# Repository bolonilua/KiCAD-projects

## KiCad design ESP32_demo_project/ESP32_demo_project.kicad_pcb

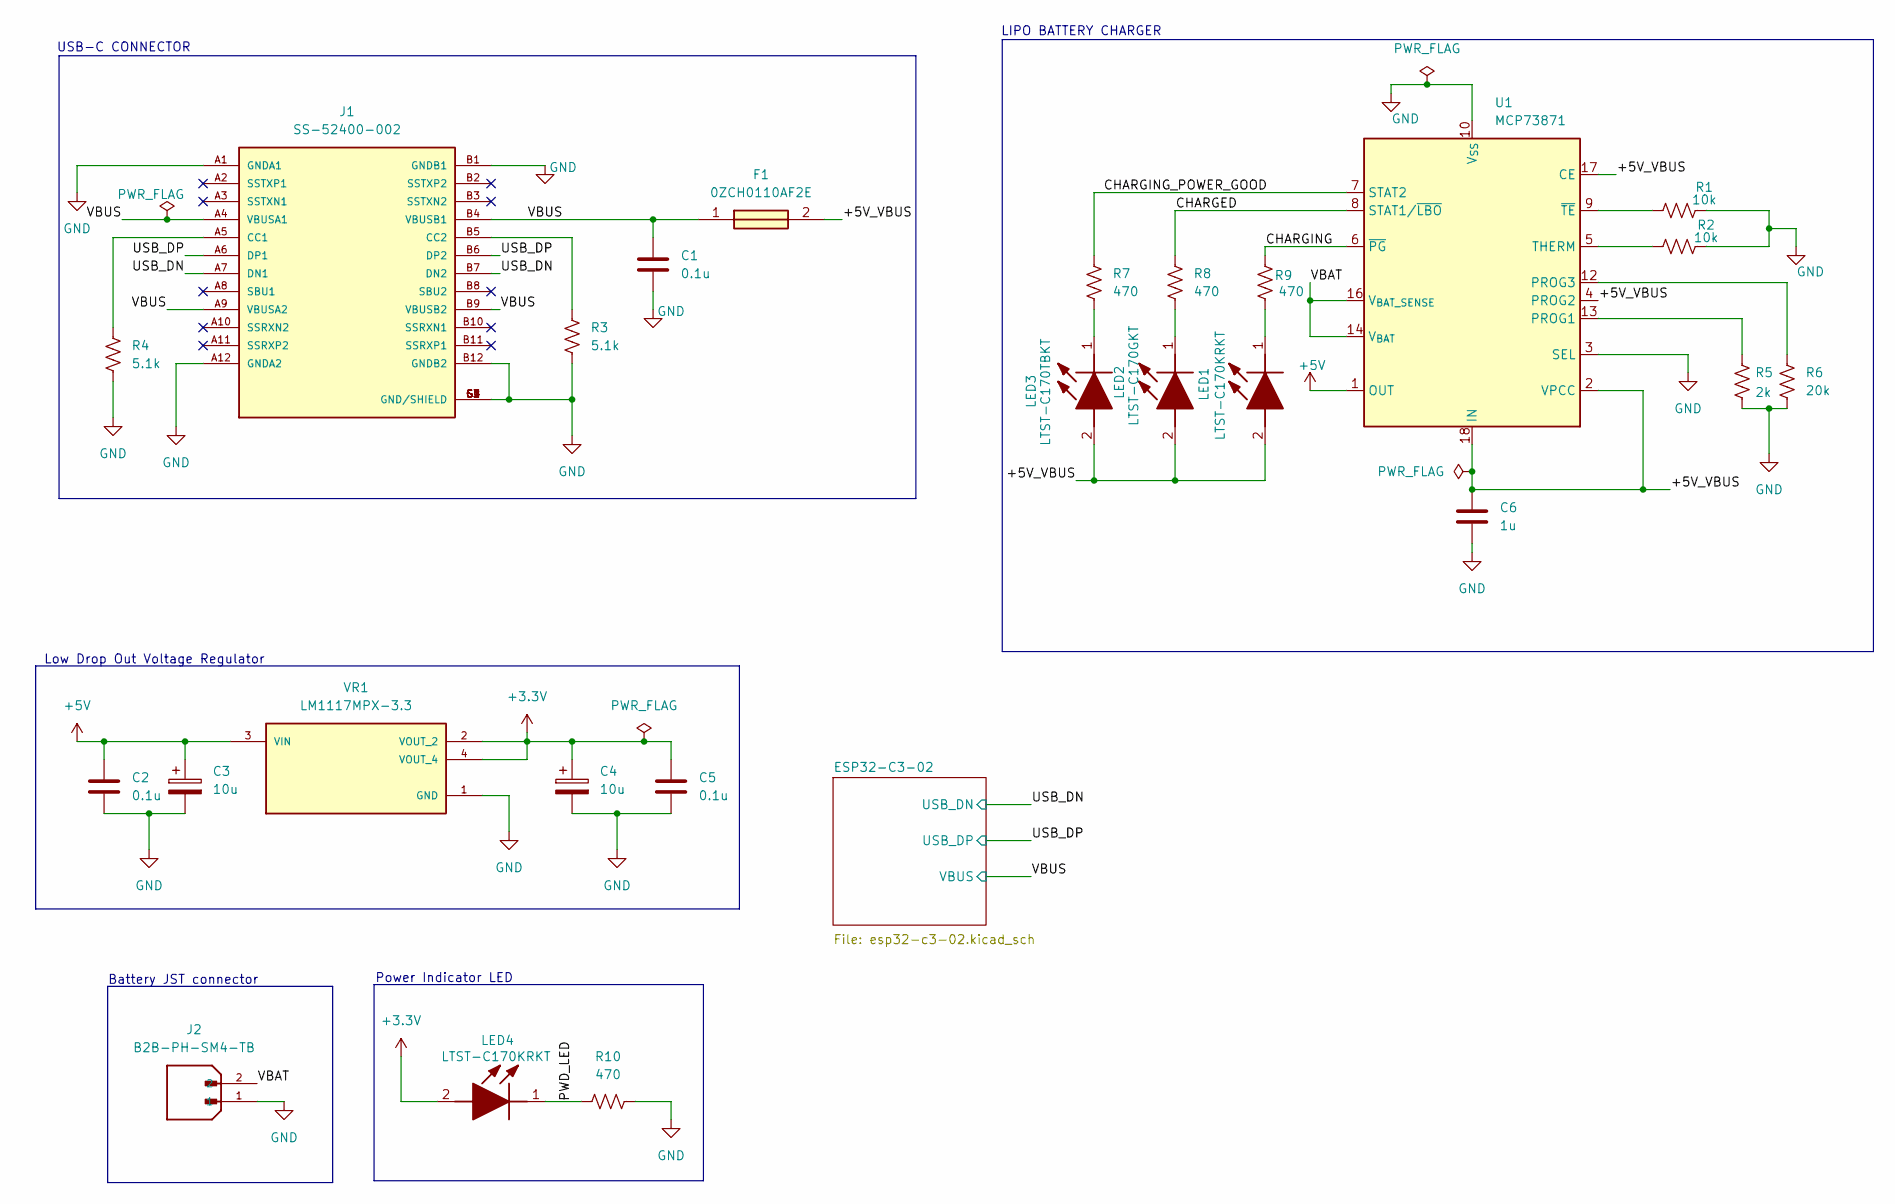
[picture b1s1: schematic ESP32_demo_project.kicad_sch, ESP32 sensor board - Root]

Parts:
C1, C2, C5: 0.1u; C_0805_2012Metric
C3, C4: 10u; T491A
C6: 1u; C_0805_2012Metric
F1: 0ZCH0110AF2E; FUSC3226X100N; Manufacturer_Part_Number 0ZCH0110AF2E
J1: SS-52400-002; BELFUSE_SS-52400-002; PARTREV A0
J2: B2B-PH-SM4-TB; JST_B2B-PH-SM4-TB; PARTREV N/A
LED1, LED4: LTST-C170KRKT; LEDC2012X120N; Manufacturer_Part_Number LTST-C170KRKT; Mouser Part Number 859-LTST-C170KRKT
LED2: LTST-C170GKT; LEDC2012X120N; Manufacturer_Part_Number LTST-C170GKT; Mouser Part Number 859-LTST-C170GKT
LED3: LTST-C170TBKT; LEDC2012X120N; Manufacturer_Part_Number LTST-C170TBKT; Mouser Part Number 859-LTST-C170TBKT
R1, R2: 10k; R_0805_2012Metric
R3, R4: 5.1k; R_0805_2012Metric
R5: 2k; R_0805_2012Metric
R6: 20k; R_0805_2012Metric
R7, R8, R9, R10: 470; R_0805_2012Metric
U1: MCP73871; QFN-20-1EP_4x4mm_P0.5mm_EP2.5x2.5mm
VR1: LM1117MPX-3.3; VREG_LM1117MPX-3.3

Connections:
+3.3V: C4.1, C5.1, LED4.2 (A), VR1.2 (VOUT_2), VR1.4 (VOUT_4); also elsewhere on the board
+5V: C2.1, C3.1, U1.1 (OUT), U1.20 (OUT), VR1.3 (VIN)
/+5V_VBUS: C6.1, F1.2, LED1.2 (A), LED2.2 (A), LED3.2 (A), U1.2 (VPCC), U1.4 (PROG2), U1.17 (CE), U1.18 (IN), U1.19 (IN)
/CHARGED: R8.1, U1.8 (STAT1/~LBO)
/CHARGING: R9.1, U1.6 (~PG)
/CHARGING_POWER_GOOD: R7.1, U1.7 (STAT2)
/PWD_LED: LED4.1 (K), R10.1
/USB_DN: J1.A7 (DN1), J1.B7 (DN2); also elsewhere on the board
/USB_DP: J1.A6 (DP1), J1.B6 (DP2); also elsewhere on the board
/VBAT: J2.2, U1.14 (V_{BAT}), U1.15 (V_{BAT}), U1.16 (V_{BAT_SENSE})
/VBUS: C1.1, F1.1, J1.A4 (VBUSA1), J1.A9 (VBUSA2), J1.B4 (VBUSB1), J1.B9 (VBUSB2); also elsewhere on the board
GND: C1.2, C2.2, C3.2, C4.2, C5.2, C6.2, J1.A1 (GNDA1), J1.A12 (GNDA2), J1.B1 (GNDB1), J1.B12 (GNDB2), J1.G1 (GND/SHIELD), J1.G2 (GND/SHIELD), J1.G3 (GND/SHIELD), J1.G4 (GND/SHIELD), J1.S1 (GND/SHIELD), J1.S2 (GND/SHIELD), J1.S3 (GND/SHIELD), J1.S4 (GND/SHIELD), J2.1, R1.2, R2.2, R3.2, R4.2, R5.2, R6.1, R10.2, U1.3 (SEL), U1.10 (V_{SS}), U1.11 (V_{SS}), U1.21 (V_{SS}), VR1.1 (GND); also elsewhere on the board
unnamed: J1.A5 (CC1), R4.1
unnamed: J1.B5 (CC2), R3.1
unnamed: LED1.1 (K), R9.2
unnamed: LED2.1 (K), R8.2
unnamed: LED3.1 (K), R7.2
unnamed: R5.1, U1.13 (PROG1)
unnamed: R6.2, U1.12 (PROG3)
unnamed: R2.1, U1.5 (THERM)
unnamed: R1.1, U1.9 (~TE)

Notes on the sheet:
LIPO BATTERY CHARGER
Power Indicator LED
Battery JST connector
Low Drop Out Voltage Regulator
USB-C CONNECTOR

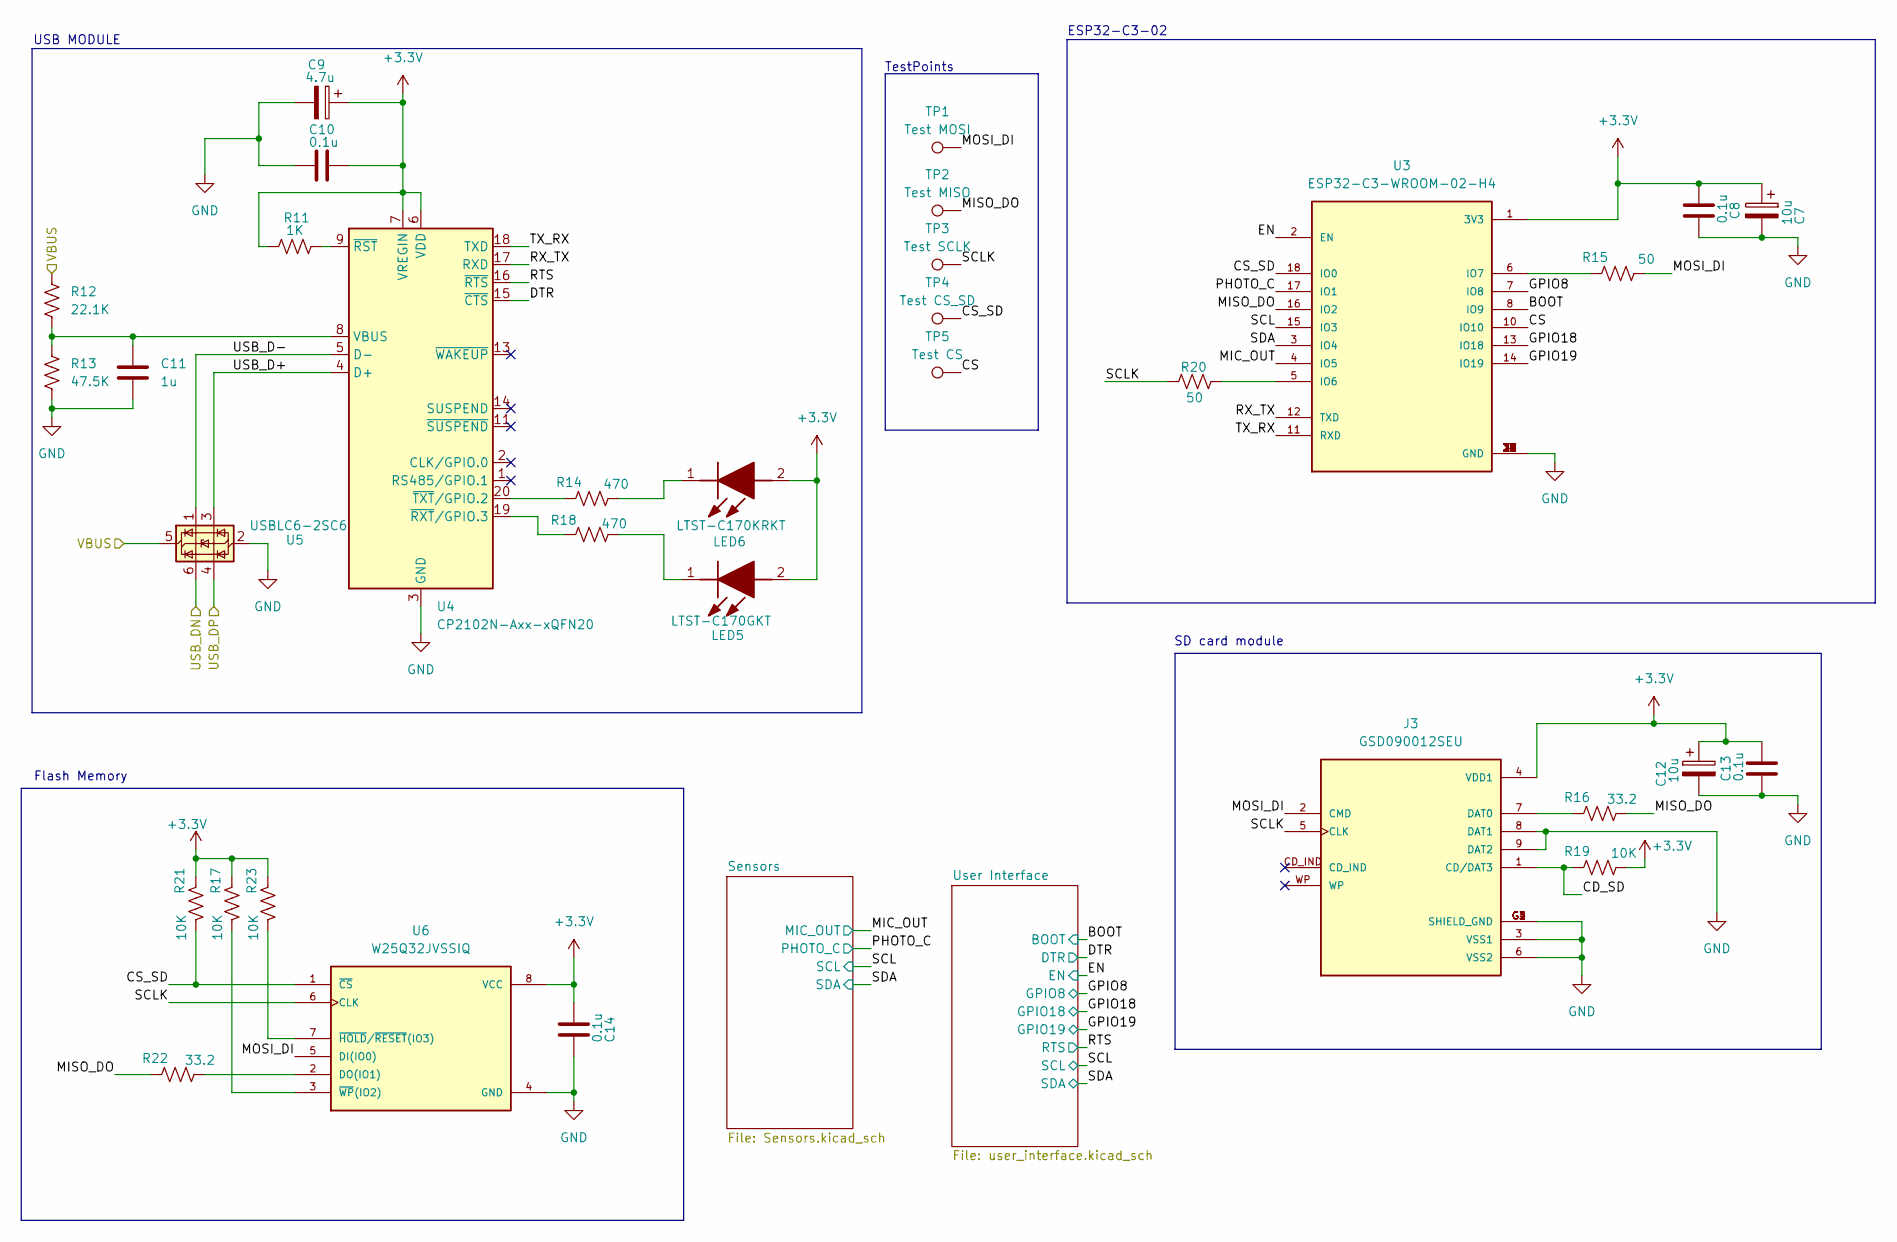
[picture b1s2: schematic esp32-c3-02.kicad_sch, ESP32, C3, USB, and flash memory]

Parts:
C7, C12: 10u; T491A
C8, C10, C13, C14: 0.1u; C_0805_2012Metric
C9: 4.7u; T491A
C11: 1u; C_0805_2012Metric
J3: GSD090012SEU; AMPHENOL_GSD090012SEU; PARTREV E
LED5: LTST-C170GKT; LEDC2012X120N; Manufacturer_Part_Number LTST-C170GKT; Mouser Part Number 859-LTST-C170GKT
LED6: LTST-C170KRKT; LEDC2012X120N; Manufacturer_Part_Number LTST-C170KRKT; Mouser Part Number 859-LTST-C170KRKT
R11: 1K; R_0805_2012Metric
R12: 22.1K; R_0805_2012Metric
R13: 47.5K; R_0805_2012Metric
R14, R18: 470; R_0805_2012Metric
R15, R20: 50; R_0805_2012Metric
R16, R22: 33.2; R_0805_2012Metric
R17, R19, R21, R23: 10K; R_0805_2012Metric
TP1: Test MOSI; TestPoint_Pad_D1.0mm
TP2: Test MISO; TestPoint_Pad_D1.0mm
TP3: Test SCLK; TestPoint_Pad_D1.0mm
TP4: Test CS_SD; TestPoint_Pad_D1.0mm
TP5: Test CS; TestPoint_Pad_D1.0mm
U3: ESP32-C3-WROOM-02-H4; MODULE_ESP32-C3-WROOM-02-H4
U4: CP2102N-Axx-xQFN20; SiliconLabs_QFN-20-1EP_3x3mm_P0.5mm_EP1.8x1.8mm
U5: USBLC6-2SC6; SOT-23-6
U6: W25Q32JVSSIQ; SOIC127P790X216-8N; M_PART_NUMBER W25QXX

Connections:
+3.3V: C7.1, C8.2, C9.1, C10.2, C12.1, C13.2, C14.2, J3.4 (VDD1), LED5.2 (A), LED6.2 (A), R11.1, R17.1, R19.2, R21.1, R23.1, U3.1 (3V3), U4.6 (VDD), U4.7 (VREGIN), U6.8 (VCC); also elsewhere on the board
/ESP32-C3-02/BOOT: U3.8 (IO9); also elsewhere on the board
/ESP32-C3-02/CD_SD: J3.1 (CD/DAT3), R19.1
/ESP32-C3-02/CS: TP5.1, U3.10 (IO10)
/ESP32-C3-02/CS_SD: R21.2, TP4.1, U3.18 (IO0), U6.1 (~CS)
/ESP32-C3-02/DTR: U4.15 (~CTS); also elsewhere on the board
/ESP32-C3-02/EN: U3.2 (EN); also elsewhere on the board
/ESP32-C3-02/GPIO8: U3.7 (IO8); also elsewhere on the board
/ESP32-C3-02/GPIO18: U3.13 (IO18); also elsewhere on the board
/ESP32-C3-02/GPIO19: U3.14 (IO19); also elsewhere on the board
/ESP32-C3-02/MIC_OUT: U3.4 (IO5); also elsewhere on the board
/ESP32-C3-02/MISO_DO: R16.2, R22.1, TP2.1, U3.16 (IO2)
/ESP32-C3-02/MOSI_DI: J3.2 (CMD), R15.2, TP1.1, U6.5 (DI(IO0))
/ESP32-C3-02/PHOTO_C: U3.17 (IO1); also elsewhere on the board
/ESP32-C3-02/RTS: U4.16 (~RTS); also elsewhere on the board
/ESP32-C3-02/RX_TX: U3.12 (TXD), U4.17 (RXD)
/ESP32-C3-02/SCL: U3.15 (IO3); also elsewhere on the board
/ESP32-C3-02/SCLK: J3.5 (CLK), R20.1, TP3.1, U6.6 (CLK)
/ESP32-C3-02/SDA: U3.3 (IO4); also elsewhere on the board
/ESP32-C3-02/TX_RX: U3.11 (RXD), U4.18 (TXD)
/ESP32-C3-02/USB_D+: U4.4 (D+), U5.3 (I/O2)
/ESP32-C3-02/USB_D-: U4.5 (D-), U5.1 (I/O1)
/USB_DN: U5.6 (I/O1); also elsewhere on the board
/USB_DP: U5.4 (I/O2); also elsewhere on the board
/VBUS: R12.1, U5.5 (VBUS); also elsewhere on the board
GND: C7.2, C8.1, C9.2, C10.1, C11.2, C12.2, C13.1, C14.1, J3.3 (VSS1), J3.6 (VSS2), J3.8 (DAT1), J3.9 (DAT2), J3.G1 (SHIELD_GND), J3.G2 (SHIELD_GND), J3.G3 (SHIELD_GND), J3.G4 (SHIELD_GND), R13.2, U3.9 (GND), U3.19 (GND), U3.20 (GND), U3.21 (GND), U3.22 (GND), U3.23 (GND), U3.24 (GND), U3.25 (GND), U3.26 (GND), U3.27 (GND), U3.28 (GND), U3.29 (GND), U3.30 (GND), U3.31 (GND), U3.32 (GND), U3.33 (GND), U3.34 (GND), U3.35 (GND), U3.36 (GND), U3.37 (GND), U3.38 (GND), U3.39 (GND), U4.3 (GND), U4.12 (GND), U4.21 (GND), U5.2 (GND), U6.4 (GND); also elsewhere on the board
unnamed: J3.7 (DAT0), R16.1
unnamed: LED5.1 (K), R18.2
unnamed: LED6.1 (K), R14.2
unnamed: R20.2, U3.5 (IO6)
unnamed: R15.1, U3.6 (IO7)
unnamed: C11.1, R12.2, R13.1, U4.8 (VBUS)
unnamed: R11.2, U4.9 (~RST)
unnamed: R18.1, U4.19 (~RXT/GPIO.3)
unnamed: R14.1, U4.20 (~TXT/GPIO.2)
unnamed: R22.2, U6.2 (DO(IO1))
unnamed: R23.2, U6.7 (~HOLD/~RESET(IO3))
unnamed: R17.2, U6.3 (~WP(IO2))

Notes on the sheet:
ESP32-C3-02
TestPoints
Flash Memory
USB MODULE
SD card module

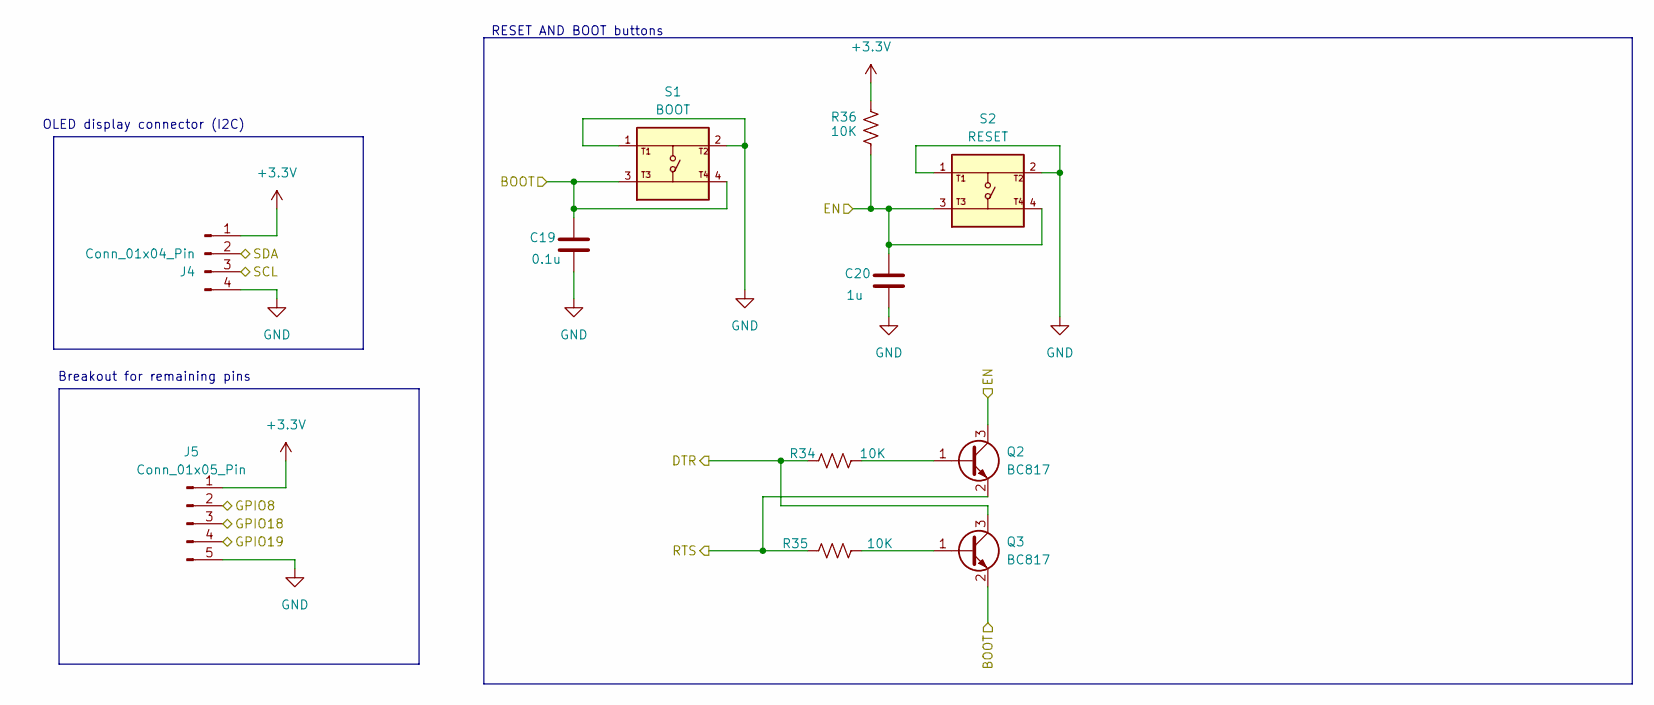
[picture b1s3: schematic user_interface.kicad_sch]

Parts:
C19: 0.1u; C_0805_2012Metric
C20: 1u; C_0805_2012Metric
J4: Conn_01x04_Pin; PinHeader_1x04_P2.54mm_Vertical
J5: Conn_01x05_Pin; PinHeader_1x05_P2.54mm_Vertical
Q2, Q3: BC817; SOT-23
R34, R35, R36: 10K; R_0805_2012Metric
S1: BOOT; SW_USLPT2819DT2TR; PARTREV P
S2: RESET; SW_USLPT2819DT2TR; PARTREV P

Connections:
+3.3V: J4.1, J5.1, R36.2; also elsewhere on the board
/ESP32-C3-02/BOOT: C19.1, Q3.2 (E), S1.3, S1.4; also elsewhere on the board
/ESP32-C3-02/DTR: Q3.3 (C), R34.1; also elsewhere on the board
/ESP32-C3-02/EN: C20.1, Q2.3 (C), R36.1, S2.3, S2.4; also elsewhere on the board
/ESP32-C3-02/GPIO8: J5.2; also elsewhere on the board
/ESP32-C3-02/GPIO18: J5.3; also elsewhere on the board
/ESP32-C3-02/GPIO19: J5.4; also elsewhere on the board
/ESP32-C3-02/RTS: Q2.2 (E), R35.1; also elsewhere on the board
/ESP32-C3-02/SCL: J4.3; also elsewhere on the board
/ESP32-C3-02/SDA: J4.2; also elsewhere on the board
GND: C19.2, C20.2, J4.4, J5.5, S1.1, S1.2, S2.1, S2.2; also elsewhere on the board
unnamed: Q2.1 (B), R34.2
unnamed: Q3.1 (B), R35.2

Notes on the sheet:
RESET AND BOOT buttons
OLED display connector (I2C)
Breakout for remaining pins

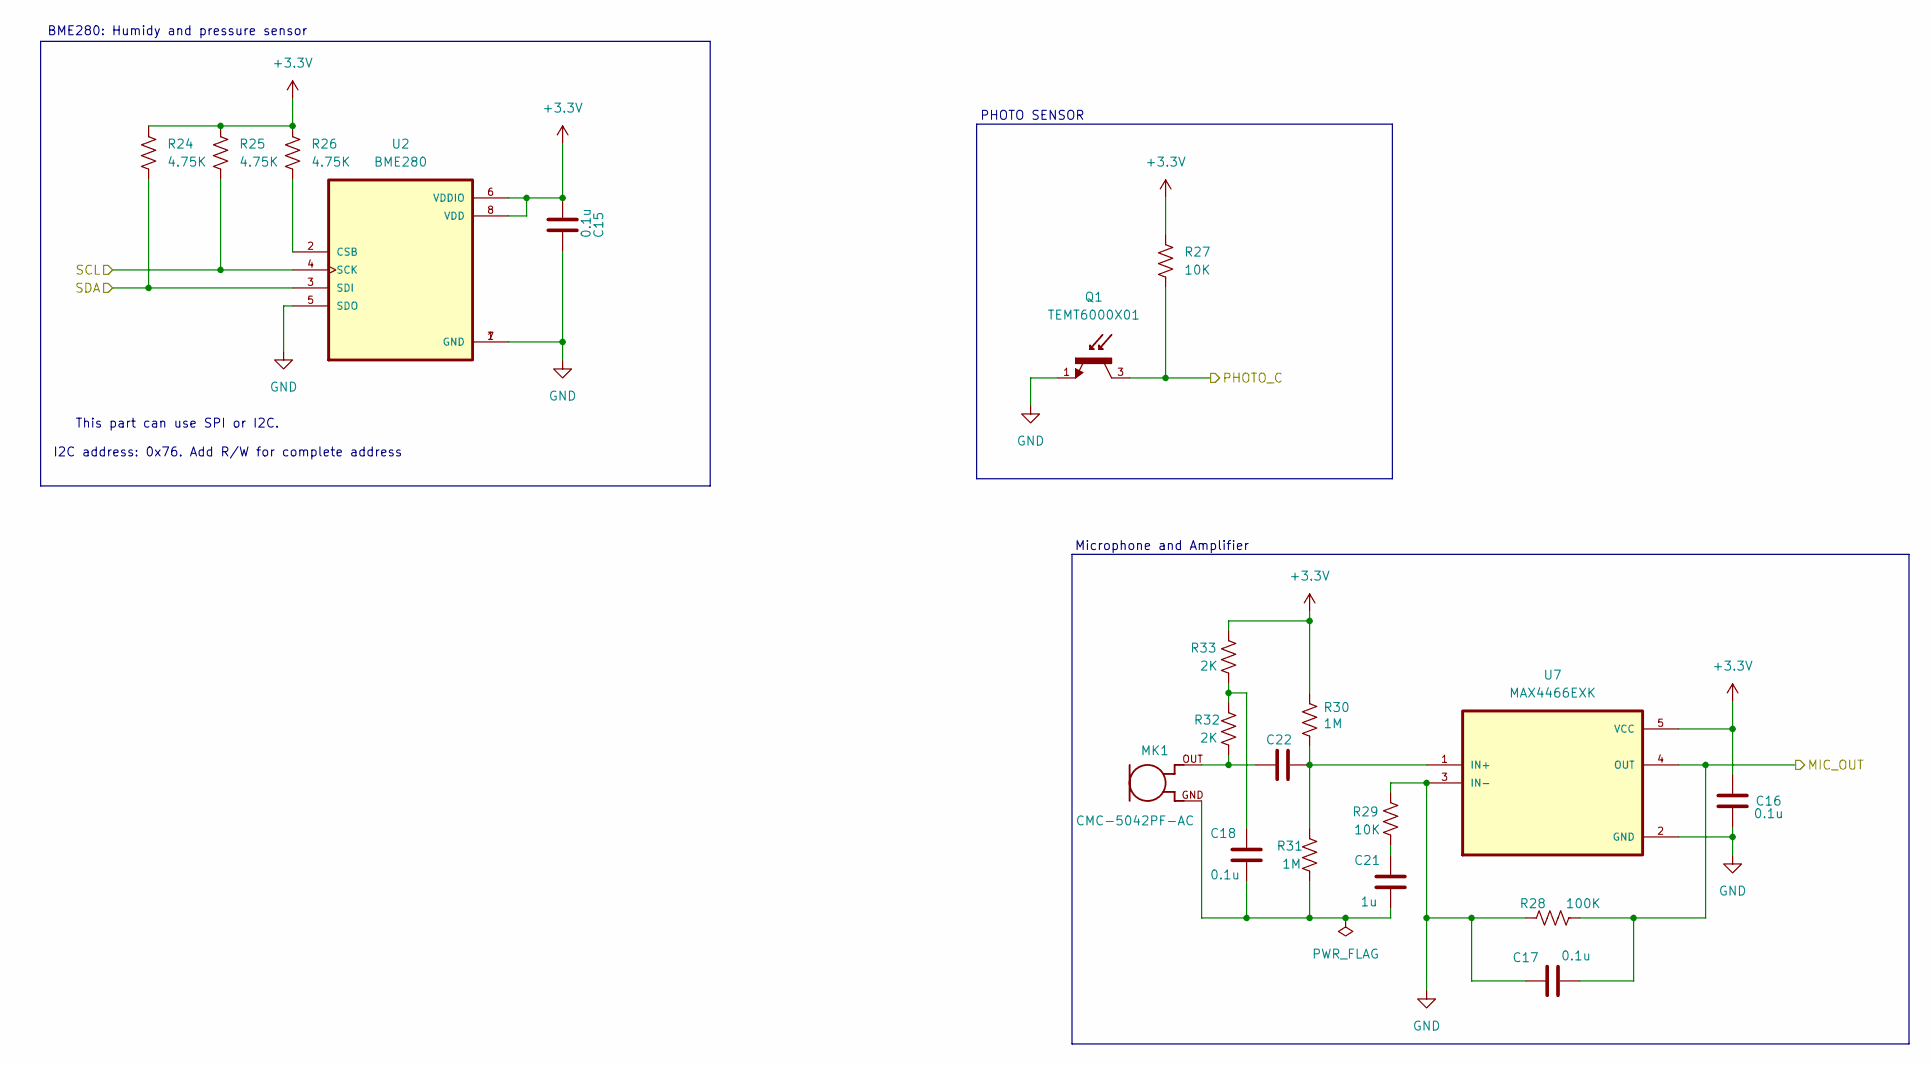
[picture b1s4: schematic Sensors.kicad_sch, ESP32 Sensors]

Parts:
C15, C16, C17, C18: 0.1u; C_0805_2012Metric
C21: 1u; C_0805_2012Metric
C22: 1n; C_0805_2012Metric
MK1: CMC-5042PF-AC; CUI_CMC-5042PF-AC
Q1: TEMT6000X01; TRANS_TEMT6000X01; PARTREV 1.9
R24, R25, R26: 4.75K; R_0805_2012Metric
R27, R29: 10K; R_0805_2012Metric
R28: 100K; R_0805_2012Metric
R30, R31: 1M; R_0805_2012Metric
R32, R33: 2K; R_0805_2012Metric
U2: BME280; PSON65P250X250X100-8N
U7: MAX4466EXK; SOT65P210X110-5N

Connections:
+3.3V: C15.2, C16.2, R24.1, R25.1, R26.1, R27.1, R30.2, R33.2, U2.6 (VDDIO), U2.8 (VDD), U7.5 (VCC); also elsewhere on the board
/ESP32-C3-02/MIC_OUT: C17.1, R28.2, U7.4 (OUT); also elsewhere on the board
/ESP32-C3-02/PHOTO_C: Q1.3, R27.2; also elsewhere on the board
/ESP32-C3-02/SCL: R25.2, U2.4 (SCK); also elsewhere on the board
/ESP32-C3-02/SDA: R24.2, U2.3 (SDI); also elsewhere on the board
GND: C15.1, C16.1, C17.2, Q1.1, R28.1, R29.2, U2.1 (GND), U2.5 (SDO), U2.7 (GND), U7.2 (GND), U7.3 (IN-); also elsewhere on the board
unnamed: C18.1, R32.2, R33.1
unnamed: C18.2, C21.2, MK1.GND, R31.1
unnamed: C21.1, R29.1
unnamed: C22.2, MK1.OUT, R32.1
unnamed: R26.2, U2.2 (CSB)
unnamed: C22.1, R30.1, R31.2, U7.1 (IN+)

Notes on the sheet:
Microphone and Amplifier
This part can use SPI or I2C.
I2C address: 0x76. Add R/W for complete address
BME280: Humidy and pressure sensor
PHOTO SENSOR

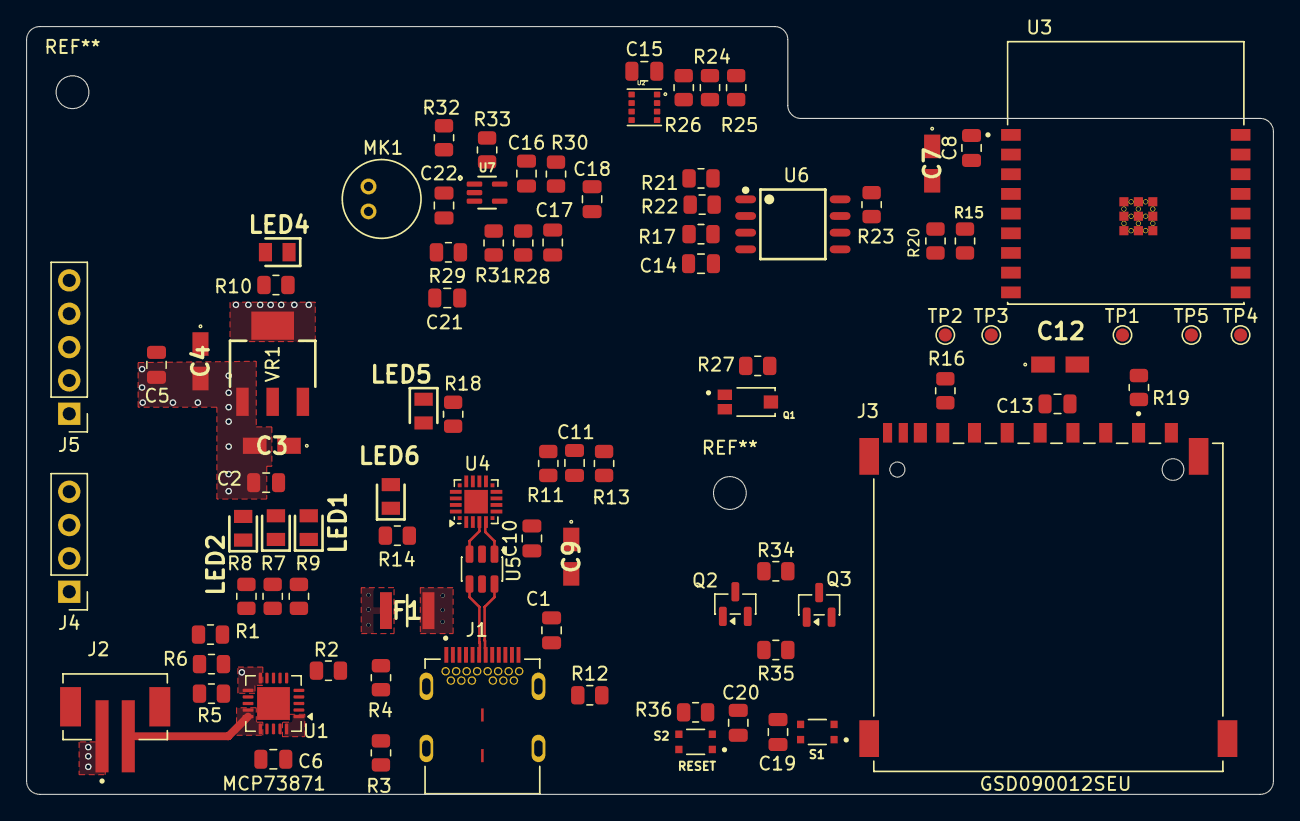
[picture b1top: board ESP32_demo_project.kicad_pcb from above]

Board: 4 copper layers, 95.0 x 58.5 mm, 89 parts (0 on the bottom side), 62 nets.

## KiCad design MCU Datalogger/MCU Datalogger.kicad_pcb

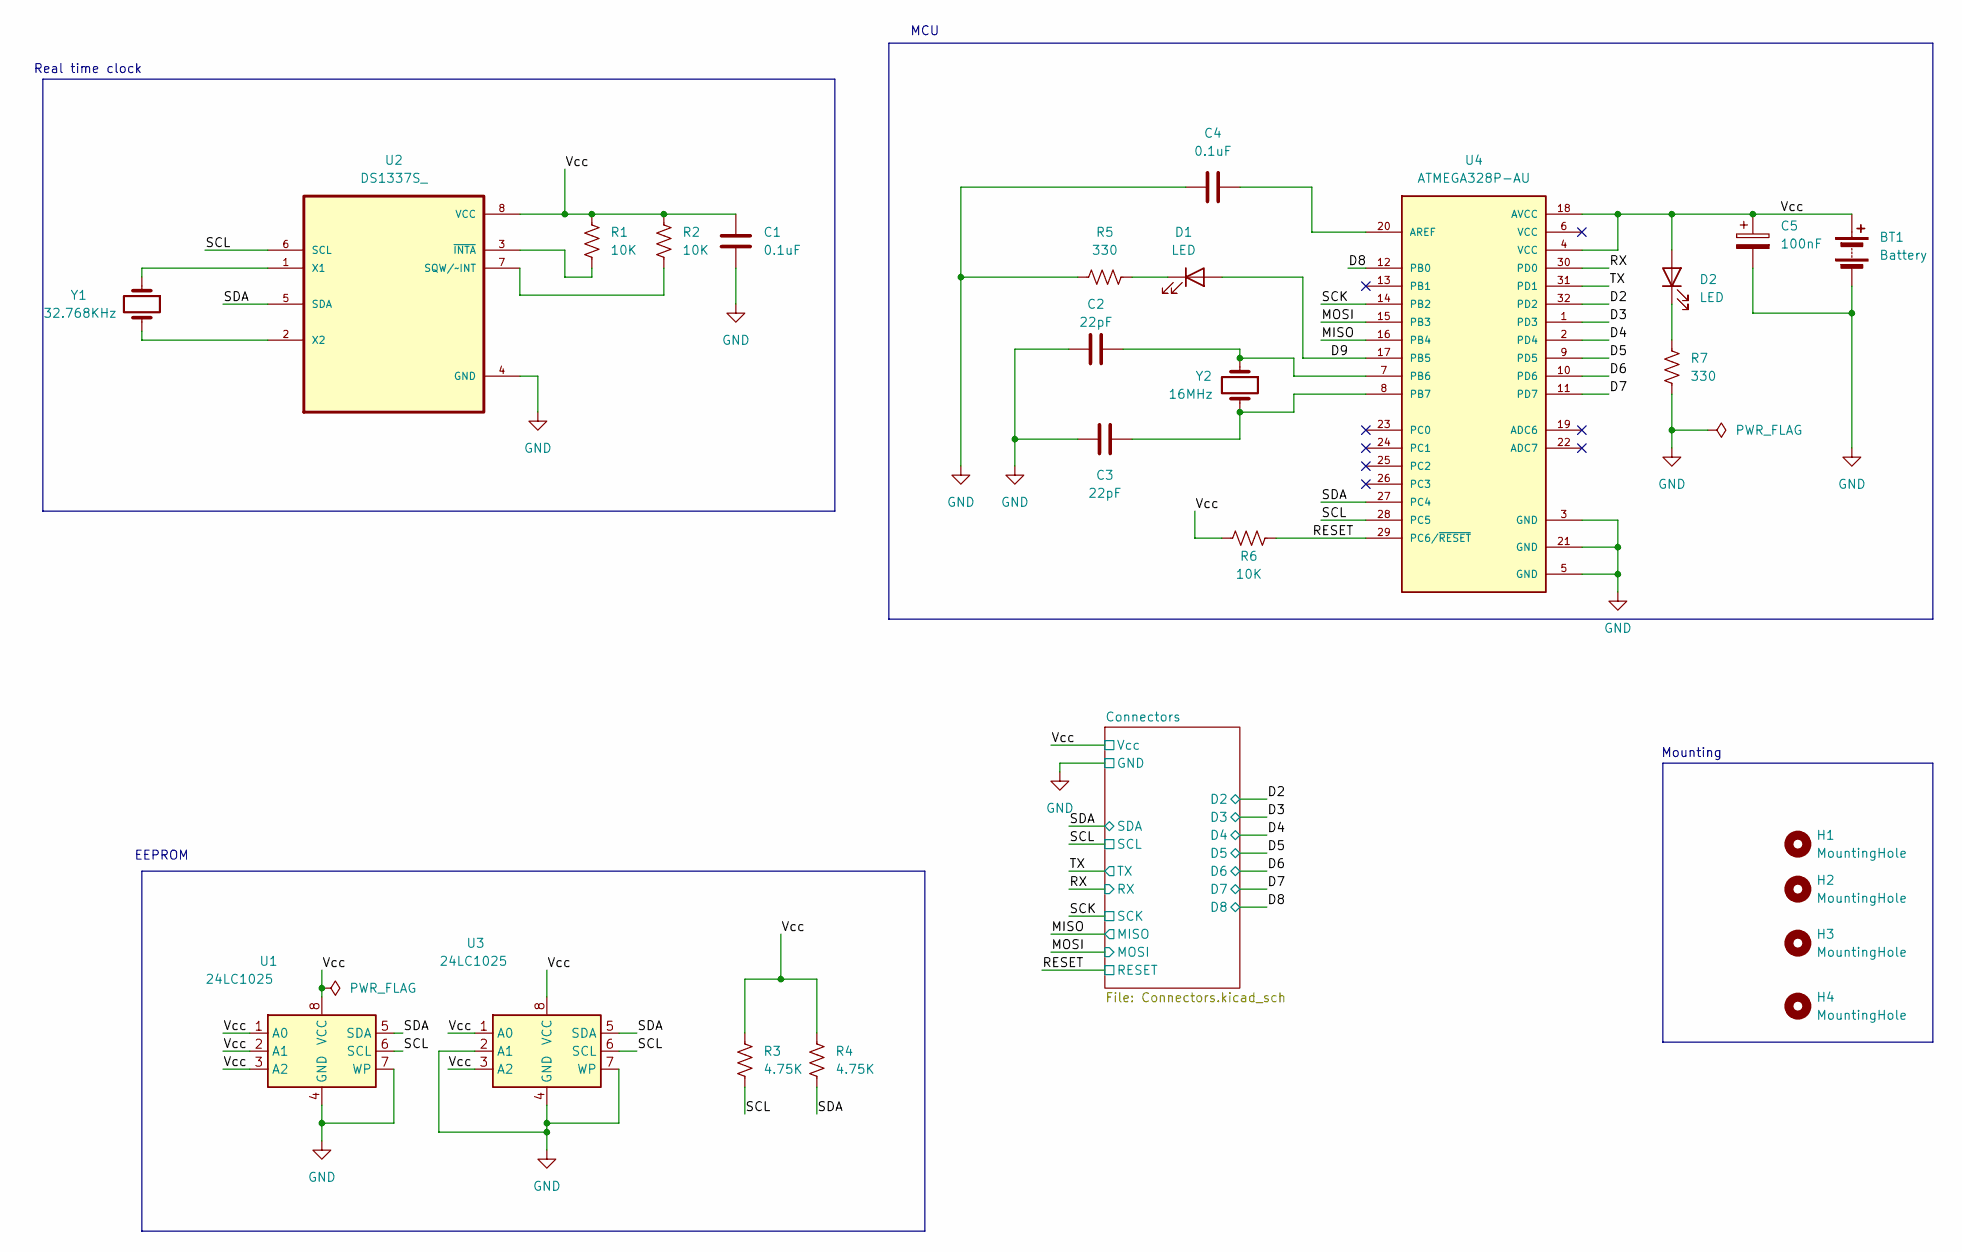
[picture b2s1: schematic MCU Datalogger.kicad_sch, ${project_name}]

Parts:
BT1: Battery; PinHeader_1x02_P2.54mm_Vertical
C1, C4: 0.1uF; C_0805_2012Metric
C2, C3: 22pF; C_0805_2012Metric
C5: 100nF; C_0805_2012Metric
D1, D2: LED; LED_0805_2012Metric
H1, H2, H3, H4: MountingHole; MountingHole_2.1mm
R1, R2, R6: 10K; R_0805_2012Metric
R3, R4: 4.75K; R_0805_2012Metric
R5, R7: 330; R_0805_2012Metric
U1, U3: 24LC1025; SOIC-8_5.3x5.3mm_P1.27mm
U2: DS1337S_; SOIC127P600X175-8N
U4: ATMEGA328P-AU; QFP80P900X900X120-32N; PARTREV 8271A
Y1: 32.768KHz; Crystal_SMD_5032-2Pin_5.0x3.2mm_HandSoldering
Y2: 16MHz; Crystal_SMD_5032-2Pin_5.0x3.2mm_HandSoldering

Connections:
/D2: U4.32 (PD2); also elsewhere on the board
/D3: U4.1 (PD3); also elsewhere on the board
/D4: U4.2 (PD4); also elsewhere on the board
/D5: U4.9 (PD5); also elsewhere on the board
/D6: U4.10 (PD6); also elsewhere on the board
/D7: U4.11 (PD7); also elsewhere on the board
/D8: U4.12 (PB0); also elsewhere on the board
/D9: D1.2 (A), U4.17 (PB5)
/MISO: U4.16 (PB4); also elsewhere on the board
/MOSI: U4.15 (PB3); also elsewhere on the board
/RESET: R6.2, U4.29 (PC6/~RESET); also elsewhere on the board
/RX: U4.30 (PD0); also elsewhere on the board
/SCK: U4.14 (PB2); also elsewhere on the board
/SCL: R3.2, U1.6 (SCL), U2.6 (SCL), U3.6 (SCL), U4.28 (PC5); also elsewhere on the board
/SDA: R4.2, U1.5 (SDA), U2.5 (SDA), U3.5 (SDA), U4.27 (PC4); also elsewhere on the board
/TX: U4.31 (PD1); also elsewhere on the board
/Vcc: BT1.1 (+), C1.1, C5.1, D2.2 (A), R1.1, R2.1, R3.1, R4.1, R6.1, U1.1 (A0), U1.2 (A1), U1.3 (A2), U1.8 (VCC), U2.8 (VCC), U3.1 (A0), U3.3 (A2), U3.8 (VCC), U4.4 (VCC), U4.18 (AVCC); also elsewhere on the board
GND: BT1.2 (-), C1.2, C2.1, C3.1, C4.1, C5.2, R5.1, R7.2, U1.4 (GND), U1.7 (WP), U2.4 (GND), U3.2 (A1), U3.4 (GND), U3.7 (WP), U4.3 (GND), U4.5 (GND), U4.21 (GND); also elsewhere on the board
unnamed: D1.1 (K), R5.2
unnamed: D2.1 (K), R7.1
unnamed: R2.2, U2.7 (SQW/~INT)
unnamed: U2.1 (X1), Y1.1
unnamed: U2.2 (X2), Y1.2
unnamed: R1.2, U2.3 (~INTA)
unnamed: C4.2, U4.20 (AREF)
unnamed: C2.2, U4.7 (PB6), Y2.1
unnamed: C3.2, U4.8 (PB7), Y2.2

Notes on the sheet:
Mounting
EEPROM
Real time clock
MCU

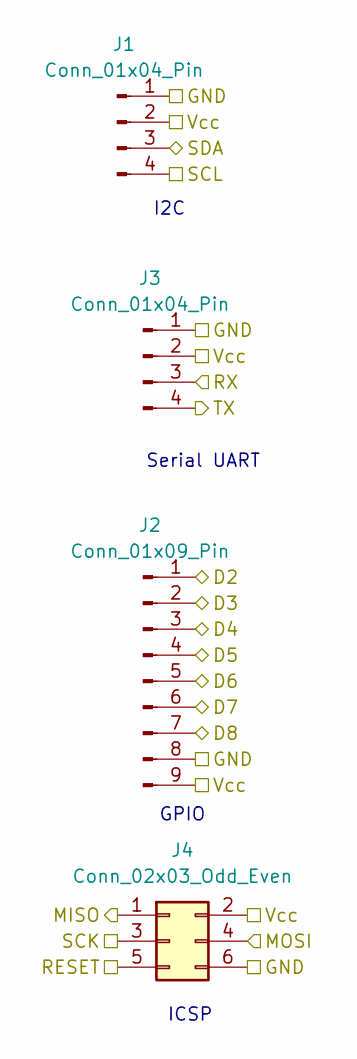
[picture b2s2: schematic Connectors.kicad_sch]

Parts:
J1, J3: Conn_01x04_Pin; PinHeader_1x04_P2.54mm_Vertical
J2: Conn_01x09_Pin; PinHeader_1x09_P2.54mm_Vertical
J4: Conn_02x03_Odd_Even; PinHeader_2x03_P2.54mm_Vertical

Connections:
/D2: J2.1; also elsewhere on the board
/D3: J2.2; also elsewhere on the board
/D4: J2.3; also elsewhere on the board
/D5: J2.4; also elsewhere on the board
/D6: J2.5; also elsewhere on the board
/D7: J2.6; also elsewhere on the board
/D8: J2.7; also elsewhere on the board
/MISO: J4.1; also elsewhere on the board
/MOSI: J4.4; also elsewhere on the board
/RESET: J4.5; also elsewhere on the board
/RX: J3.3; also elsewhere on the board
/SCK: J4.3; also elsewhere on the board
/SCL: J1.4; also elsewhere on the board
/SDA: J1.3; also elsewhere on the board
/TX: J3.4; also elsewhere on the board
/Vcc: J1.2, J2.9, J3.2, J4.2; also elsewhere on the board
GND: J1.1, J2.8, J3.1, J4.6; also elsewhere on the board

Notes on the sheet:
I2C
Serial UART
GPIO
ICSP

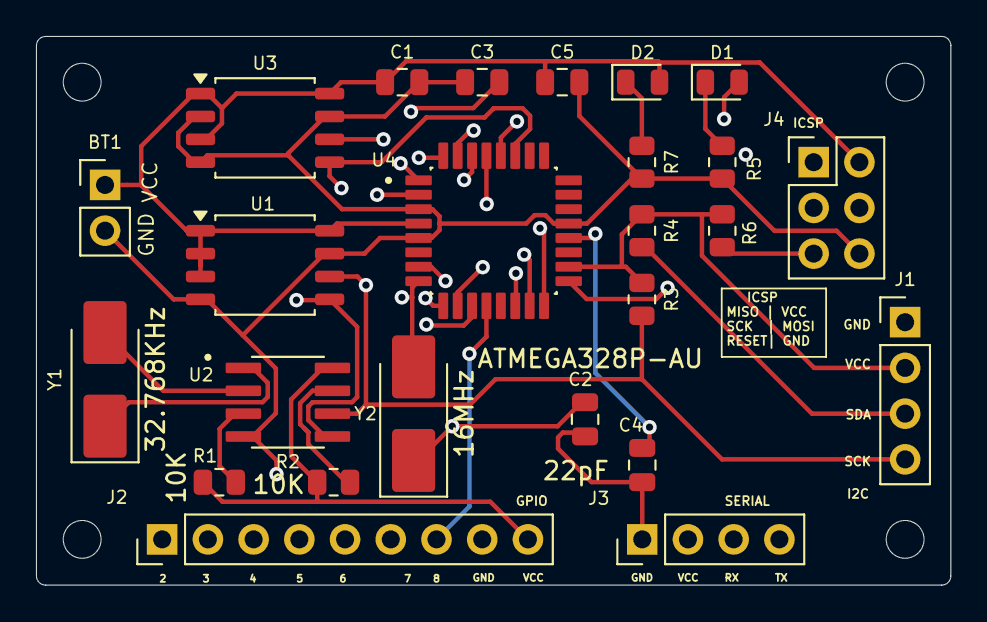
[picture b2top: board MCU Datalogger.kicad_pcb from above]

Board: 4 copper layers, 50.8 x 30.5 mm, 29 parts (0 on the bottom side), 27 nets.

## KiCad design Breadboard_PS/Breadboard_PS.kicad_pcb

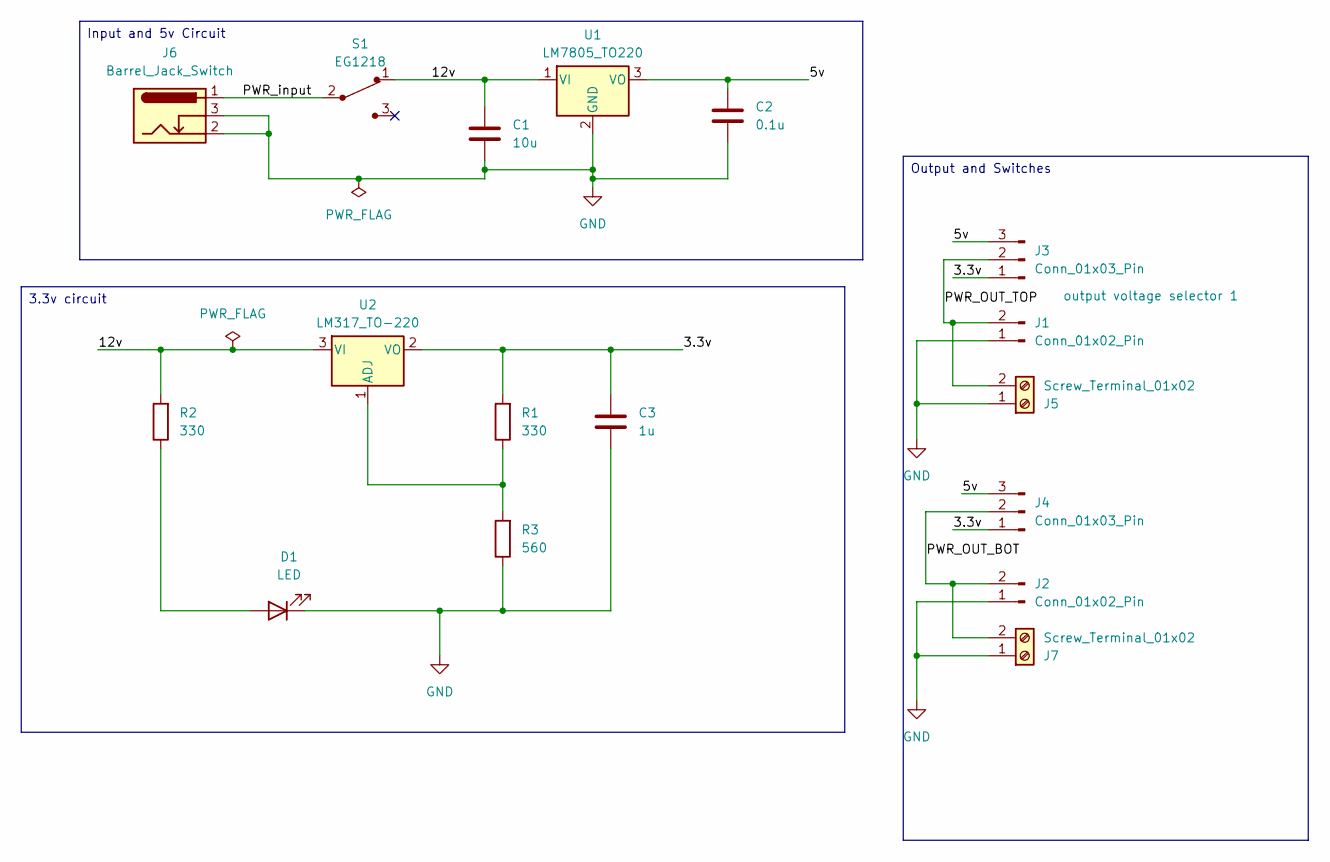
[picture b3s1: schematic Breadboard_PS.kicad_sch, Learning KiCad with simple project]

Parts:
C1: 10u; C_Disc_D3.0mm_W1.6mm_P2.50mm
C2: 0.1u; C_Disc_D3.0mm_W1.6mm_P2.50mm
C3: 1u; C_Disc_D3.0mm_W1.6mm_P2.50mm
D1: LED; LED_D5.0mm
J1, J2: Conn_01x02_Pin; PinHeader_1x02_P2.54mm_Vertical
J3, J4: Conn_01x03_Pin; PinHeader_1x03_P2.54mm_Vertical
J5, J7: Screw_Terminal_01x02; TerminalBlock_bornier-2_P5.08mm
J6: Barrel_Jack_Switch; BarrelJack_Horizontal
R1, R2: 330; R_Axial_DIN0204_L3.6mm_D1.6mm_P5.08mm_Horizontal
R3: 560; R_Axial_DIN0204_L3.6mm_D1.6mm_P5.08mm_Horizontal
S1: EG1218; Switch_Slide_11.6x4mm_EG1218; MPN EG1218; Digi-Key_PN EG1903-ND
U1: LM7805_TO220; TO-220-3_Vertical
U2: LM317_TO-220; TO-220-3_Vertical

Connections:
/3.3v: C3.1, J3.1, J4.1, R1.2, U2.2 (VO)
/5v: C2.1, J3.3, J4.3, U1.3 (VO)
/12v: C1.1, R2.2, S1.1, U1.1 (VI), U2.3 (VI)
/PWR_OUT_BOT: J2.2, J4.2, J7.2
/PWR_OUT_TOP: J1.2, J3.2, J5.2
/PWR_input: J6.1, S1.2
GND: C1.2, C2.2, C3.2, D1.1 (K), J1.1, J2.1, J5.1, J6.2, J6.3, J7.1, R3.1, U1.2 (GND)
unnamed: D1.2 (A), R2.1
unnamed: R1.1, R3.2, U2.1 (ADJ)

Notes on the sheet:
Input and 5v Circuit
3.3v circuit
Output and Switches

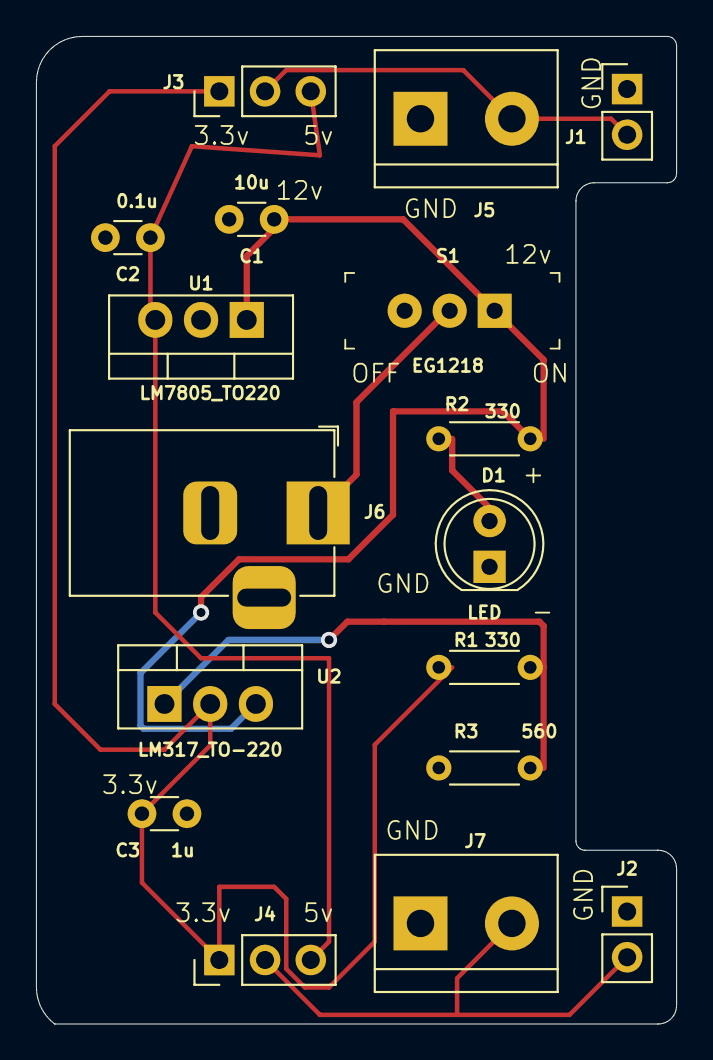
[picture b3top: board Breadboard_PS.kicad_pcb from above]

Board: 2 copper layers, 35.6 x 54.9 mm, 17 parts (0 on the bottom side), 9 nets.
